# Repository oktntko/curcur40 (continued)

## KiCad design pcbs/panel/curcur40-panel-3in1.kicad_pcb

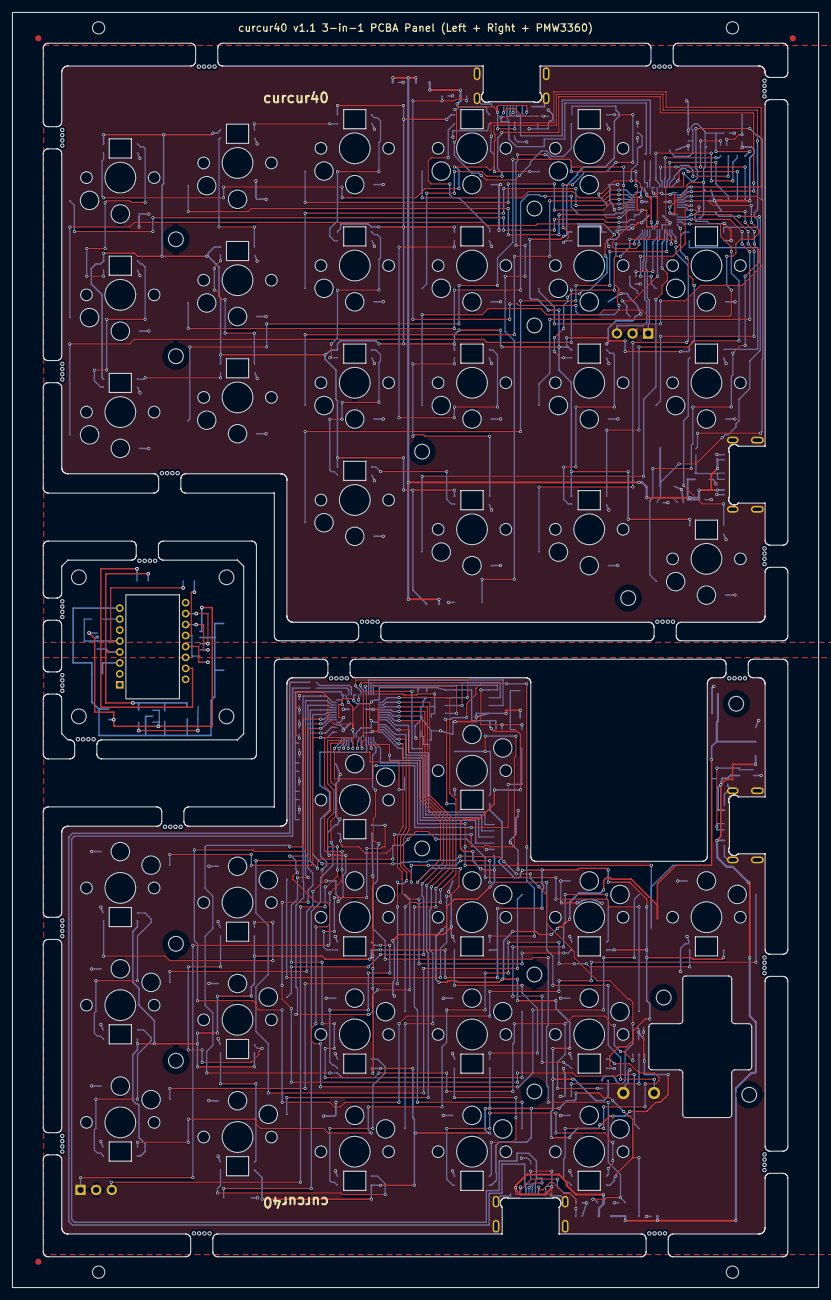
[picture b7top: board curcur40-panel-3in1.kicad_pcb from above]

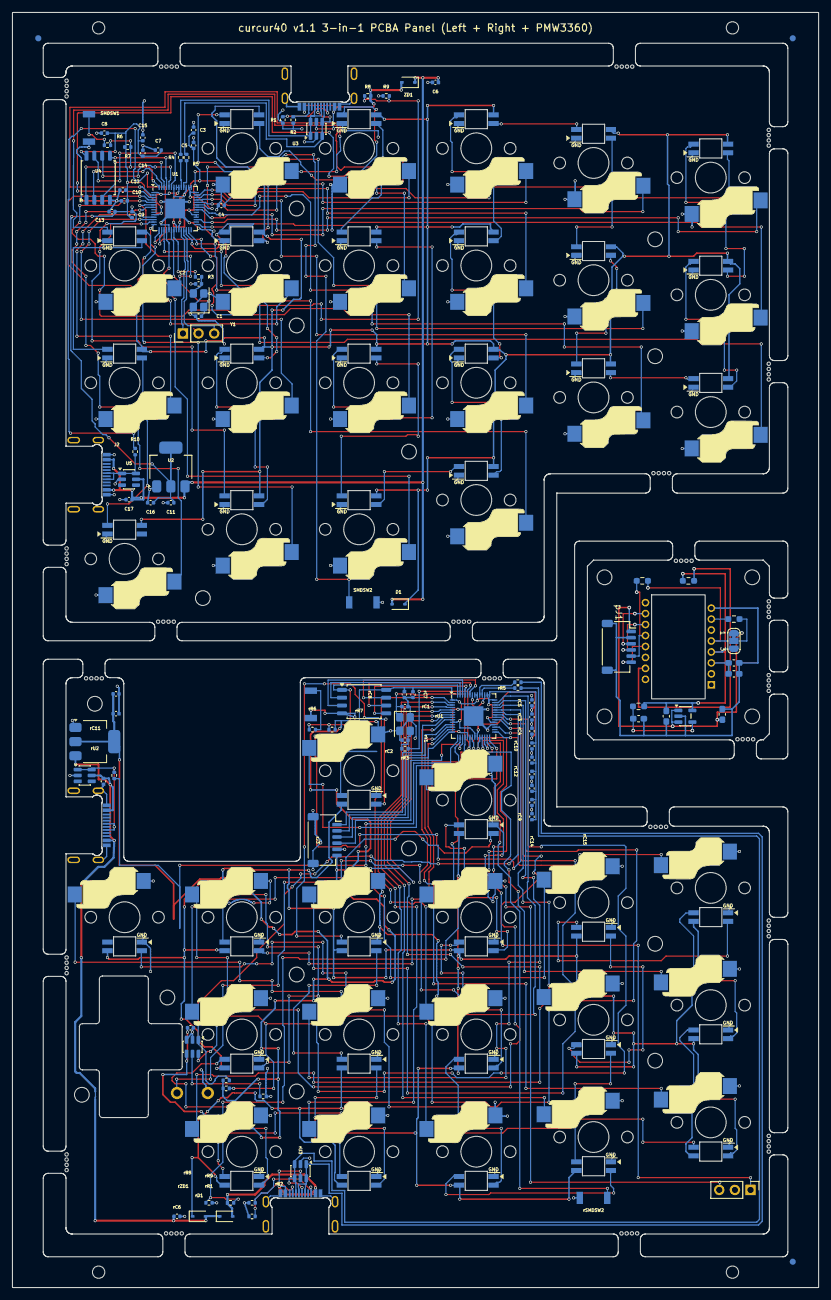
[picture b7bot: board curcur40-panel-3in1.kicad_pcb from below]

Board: 2 copper layers, 131.0 x 207.2 mm, 276 parts (181 on the bottom side), 154 nets.

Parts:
C1, C2: 27p; C_0402_1005Metric
C3, C4, C7, C9, C10, C12, C13, C14, C15: 100n; C_0402_1005Metric
C5, C8, C16, C17: 1u; C_0402_1005Metric
C6, C11: 10u; C_0402_1005Metric
D1: 1N4148WS; D_SOD-323
EXLED1, EXLED2, EXLED3: YS-SK6812MINI-E
EXSW1, EXSW2, EXSW3: SW_Push; keyswitch_choc12_hotswap_1u
FID1_B, FID1_F, FID2_B, FID2_F, FID3_B, FID3_F: Fiducial_1mm_Mask2mm
J1, J2: TYPE-C-31-M-13C; USB_C_Receptacle_TYPE-C-31-M-13C
J4: Conn_01x03; PinHeader_1x03_P2.54mm_Vertical
LED1, LED2, LED3, LED4, LED5, LED6, LED7, LED8, LED9, LED10, LED11, LED12, LED13, LED14, LED15, LED16, LED17, LED18: YS-SK6812MINI-E
MB1, MB2, MB3, MB4, MB5, MB6, MB7, MB8, MB9, MB10, MB11, MB12, MB13, MB14, MB15, MB16, MB17, MB18, MB19, MB20, MB21, MB22, MB23, MB24, MB25, MB26, MB27, MB28, MB29, MB30, MB31, MB32, MB33, MB34, MB35, MB36, MB37, MB38, MB39, MB40, MB41, MB42, MB43, MB44, MB45, MB46, MB47, MB48, MB49, MB50, MB51, MB52, MB53, MB54, MB55, MB56, MB57, MB58, MB59, MB60, MB61, MB62, MB63, MB64, MB65, MB66, MB67, MB68, MB69, MB70, MB71, MB72, MB73, MB74, MB75, MB76, MB77, MB78, MB79, MB80, MB81, MB82, MB83, MB84, MB85, MB86, MB87, MB88: NPTH
R1, R2: 5.1k; R_0402_1005Metric
R3, R6: 1k; R_0402_1005Metric
R4, R5, R10: 27; R_0402_1005Metric
R7: 10k; R_0402_1005Metric
R8: 5.6k; R_0402_1005Metric
R9: 10K; R_0402_1005Metric
SMDSW1, SMDSW2: TS-1088R-02026
SW1, SW2, SW3, SW4, SW5, SW6, SW7, SW8, SW9, SW10, SW11, SW12, SW13, SW14, SW15, SW16, SW17, SW18: SW_Push; keyswitch_choc12_hotswap_1u
TH1, TH2, TH3, TH4: NPTH
U1: RP2040; QFN-56-1EP_7x7mm_P0.4mm_EP3.2x3.2mm
U2: LDL1117S33R; SOT-223-3_TabPin2
U3, U5: USBLC6-2SC6; SOT-23-6
U4: W25Q128JVSIQ; SOIC-8_5.3x5.3mm_P1.27mm
Y1: 12MHz 18pF; Crystal_SMD_3225-4Pin_3.2x2.5mm
ZD1: 1N5819WS; D_SOD-323
pC1: 4.7uF/10V; C_0603_1608Metric_Pad1.08x0.95mm_HandSolder
pC2: 100nF; C_0603_1608Metric_Pad1.08x0.95mm_HandSolder
pC3, pC4: 1uF; C_0603_1608Metric_Pad1.08x0.95mm_HandSolder
pC5: 22nF; C_0603_1608Metric_Pad1.08x0.95mm_HandSolder
pJ1: SM06B-SRSS-TB; JST_SH_SM06B-SRSS-TB_1x06-1MP_P1.00mm_Horizontal
pJP1: SolderJumper_3_Bridged12; SolderJumper-3_P1.3mm_Bridged12_RoundedPad1.0x1.5mm_NumberL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
pR1, pR2: 10k; R_0603_1608Metric_Pad0.98x0.95mm_HandSolder
pR3: 39R; R_0603_1608Metric_Pad0.98x0.95mm_HandSolder
pR4: 28k; R_0603_1608Metric_Pad0.98x0.95mm_HandSolder
pU1: PMW3360DM-T2QU; PMW3360DM-T2QU_16Pin
pU2: TLV74318PDBVR; SOT-23-5
rC1, rC2: 27p; C_0402_1005Metric
rC3, rC4, rC7, rC9, rC10, rC12, rC13, rC14, rC15, rC18: 100n; C_0402_1005Metric
rC5, rC8, rC16, rC17: 1u; C_0402_1005Metric
rC6, rC11: 10u; C_0402_1005Metric
rD1: 1N4148WS; D_SOD-323
rEXLED2: YS-SK6812MINI-E
rEXSW1: Kailh_Square_Silent; Kailh_Square_Silent_6.2x6.2mm
rEXSW2: SW_Push; keyswitch_choc12_hotswap_1u
rJ1, rJ2: TYPE-C-31-M-13C; USB_C_Receptacle_TYPE-C-31-M-13C
rJ3: SM06B-SRSS-TB; JST_SH_SM06B-SRSS-TB_1x06-1MP_P1.00mm_Horizontal
rJ4: Conn_01x03; PinHeader_1x03_P2.54mm_Vertical
rLED2, rLED3, rLED4, rLED5, rLED6, rLED7, rLED8, rLED9, rLED10, rLED11, rLED12, rLED13, rLED14, rLED15, rLED16, rLED17, rLED18: YS-SK6812MINI-E
rR1, rR2: 5.1k; R_0402_1005Metric
rR3, rR6: 1k; R_0402_1005Metric
rR4, rR5, rR10: 27; R_0402_1005Metric
rR7: 10k; R_0402_1005Metric
rR8: 5.6k; R_0402_1005Metric
rR9: 10K; R_0402_1005Metric
rR11, rR12: 4.7k; R_0402_1005Metric
rR13: 0; R_0402_1005Metric
rSMDSW1, rSMDSW2: TS-1088R-02026
rSW2, rSW3, rSW4, rSW5, rSW6, rSW7, rSW8, rSW9, rSW10, rSW11, rSW12, rSW13, rSW14, rSW15, rSW16, rSW17, rSW18: SW_Push; keyswitch_choc12_hotswap_1u
rU1: RP2040; QFN-56-1EP_7x7mm_P0.4mm_EP3.2x3.2mm
rU2: LDL1117S33R; SOT-223-3_TabPin2
rU3, rU5: USBLC6-2SC6; SOT-23-6
rU4: W25Q128JVSIQ; SOIC-8_5.3x5.3mm_P1.27mm
rU6: TMAG5273A1QDBVR; SOT-23-6
rY1: 12MHz 18pF; Crystal_SMD_3225-4Pin_3.2x2.5mm
rZD1: 1N5819WS; D_SOD-323

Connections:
L:+1V1: C3.1, C4.1, C5.1, U1.23, U1.45, U1.50
L:+3V3: C7.1, C8.1, C9.1, C10.1, C11.1, C12.1, C13.1, C14.1, C15.1, C16.1, R7.2, U1.1, U1.10, U1.22, U1.32, U1.33, U1.42, U1.43, U1.44, U1.48, U1.49, U2.2, U4.8
L:+5V: C6.1, C17.1, D1.2, J2.A4 (VBUS), J2.A9 (VBUS), J2.B4 (VBUS), J2.B9 (VBUS), U2.3, U5.5, ZD1.1
L:/D+: J1.A6 (D+), J1.B6 (D+), R4.1, U3.1, U3.6
L:/D-: J1.A7 (D-), J1.B7 (D-), R5.2, U3.3, U3.4
L:/KEY1: SW1.1, U1.14
L:/KEY2: SW2.1, U1.12
L:/KEY3: SW3.1, U1.4
L:/KEY4: SW4.1, U1.2
L:/KEY5: SW5.1, U1.41
L:/KEY6: SW6.1, U1.3
L:/KEY7: SW7.1, U1.5
L:/KEY8: SW8.1, U1.18
L:/KEY9: SW9.1, U1.17
L:/KEY10: SW10.1, U1.40
L:/KEY11: SW11.1, U1.39
L:/KEY12: SW12.1, U1.38
L:/KEY13: SW13.1, U1.35
L:/KEY14: SW14.1, U1.36
L:/KEY15: SW15.1, U1.37
L:/KEY16: SW16.1, U1.27
L:/KEY17: SW17.1, U1.29
L:/KEY18: SW18.1, U1.31
L:/KEYEX1: EXSW1.1, U1.6
L:/KEYEX2: EXSW2.1, U1.11
L:/KEYEX3: EXSW3.1, U1.7
L:/LED: LED1.4, U1.13
L:/QSPI_SCLK: U1.52, U4.6
L:/QSPI_SD0: U1.53, U4.5
L:/QSPI_SD1: U1.55, U4.2
L:/QSPI_SD2: U1.54, U4.3
L:/QSPI_SD3: U1.51, U4.7
L:/QSPI_SS: R6.1, R7.1, U1.56, U4.1
L:/SPLIT_DP: J2.A6 (D+), J2.B6 (D+), R10.1, U5.1, U5.6
L:/SWCLK: J4.1, U1.24
L:/SWD: J4.3, U1.25
L:/TX: R10.2, U1.15
L:/USB_VBUS_PIN: R8.2, R9.1, U1.16
L:GND: C1.2, C2.2, C3.2, C4.2, C5.2, C6.2, C7.2, C8.2, C9.2, C10.2, C11.2, C12.2, C13.2, C14.2, C15.2, C16.2, C17.2, EXLED1.3, EXLED2.3, EXLED3.3, EXSW1.2, EXSW2.2, EXSW3.2, J1.A1 (GND), J1.A12 (GND), J1.B1 (GND), J1.B12 (GND), J1.SH (SHIELD), J2.A1 (GND), J2.A12 (GND), J2.B1 (GND), J2.B12 (GND), J2.SH (SHIELD), J4.2, LED1.3, LED2.3, LED3.3, LED4.3, LED5.3, LED6.3, LED7.3, LED8.3, LED9.3, LED10.3, LED11.3, LED12.3, LED13.3, LED14.3, LED15.3, LED16.3, LED17.3, LED18.3, R1.1, R2.1, R9.2, SMDSW1.1, SMDSW2.1, SW1.2, SW2.2, SW3.2, SW4.2, SW5.2, SW6.2, SW7.2, SW8.2, SW9.2, SW10.2, SW11.2, SW12.2, SW13.2, SW14.2, SW15.2, SW16.2, SW17.2, SW18.2, U1.19, U1.57, U2.1, U3.2, U4.4, U5.2, Y1.2, Y1.4
L:Net-(C2-Pad1): C2.1, R3.1, Y1.3
L:Net-(D1-K): D1.1, EXLED1.1, EXLED2.1, EXLED3.1, LED1.1, LED2.1, LED3.1, LED4.1, LED5.1, LED6.1, LED7.1, LED8.1, LED9.1, LED10.1, LED11.1, LED12.1, LED13.1, LED14.1, LED15.1, LED16.1, LED17.1, LED18.1
L:Net-(EXLED1-DIN): EXLED1.4, LED18.2
L:Net-(EXLED1-DOUT): EXLED1.2, EXLED2.4
L:Net-(EXLED2-DOUT): EXLED2.2, EXLED3.4
L:Net-(J1-CC1): J1.A5 (CC1), R1.2
L:Net-(J1-CC2): J1.B5 (CC2), R2.2
L:Net-(LED1-DOUT): LED1.2, LED2.4
L:Net-(LED2-DOUT): LED2.2, LED3.4
L:Net-(LED3-DOUT): LED3.2, LED4.4
L:Net-(LED4-DOUT): LED4.2, LED5.4
L:Net-(LED5-DOUT): LED5.2, LED6.4
L:Net-(LED6-DOUT): LED6.2, LED7.4
L:Net-(LED7-DOUT): LED7.2, LED8.4
L:Net-(LED8-DOUT): LED8.2, LED9.4
L:Net-(LED10-DIN): LED9.2, LED10.4
L:Net-(LED10-DOUT): LED10.2, LED11.4
L:Net-(LED11-DOUT): LED11.2, LED12.4
L:Net-(LED12-DOUT): LED12.2, LED13.4
L:Net-(LED13-DOUT): LED13.2, LED14.4
L:Net-(LED14-DOUT): LED14.2, LED15.4
L:Net-(LED15-DOUT): LED15.2, LED16.4
L:Net-(LED16-DOUT): LED16.2, LED17.4
L:Net-(LED17-DOUT): LED17.2, LED18.4
L:Net-(R6-Pad2): R6.2, SMDSW1.2
L:Net-(U1-RUN): SMDSW2.2, U1.26
L:Net-(U1-USB_DM): R5.1, U1.46
L:Net-(U1-USB_DP): R4.2, U1.47
L:Net-(U1-XIN): C1.1, U1.20, Y1.1
L:Net-(U1-XOUT): R3.2, U1.21
L:VBUS: J1.A4 (VBUS), J1.A9 (VBUS), J1.B4 (VBUS), J1.B9 (VBUS), R8.1, U3.5, ZD1.2
P:+3V3R: pC3.1, pJ1.1, pJP1.1, pU2.1, pU2.3
P:/+1V8_PMW: pC4.1, pJP1.3, pR3.1, pR4.1, pU1.4 (VDD), pU2.5
P:/MISO: pJ1.5, pR2.2, pU1.12 (MISO)
P:/MOSI: pJ1.4, pU1.11 (MOSI)
P:/NCS: pJ1.6, pU1.13 (~CS)
P:/RESET: pR1.2, pU1.7 (~RESET)
P:/SCLK: pJ1.3, pU1.10 (SCLK)
P:/V_{IO}: pJP1.2, pR1.1, pR2.1, pU1.5 (VDDIO)
P:GNDR: pC1.2, pC2.2, pC3.2, pC4.2, pC5.2, pJ1.2, pJ1.MP, pU1.8 (GND), pU2.2
P:Net-(U1-LED_P): pR3.2, pU1.15 (LED_P)
P:Net-(U1-VDDPIX): pC1.1, pC2.1, pU1.3 (VDDPIX)
P:Net-(U2-NC): pC5.1, pR4.2, pU2.4
R:+1V1R: rC3.1, rC4.1, rC5.1, rU1.23, rU1.45, rU1.50
R:+3V3R: rC7.1, rC8.1, rC9.1, rC10.1, rC11.1, rC12.1, rC13.1, rC14.1, rC15.1, rC16.1, rC18.1, rJ3.6, rR7.2, rR11.1, rR12.1, rU1.1, rU1.10, rU1.22, rU1.33, rU1.42, rU1.43, rU1.44, rU1.48, rU1.49, rU2.2, rU4.8, rU6.4
R:+5VR: rC6.1, rC17.1, rD1.2, rJ2.A4 (VBUS), rJ2.A9 (VBUS), rJ2.B4 (VBUS), rJ2.B9 (VBUS), rU2.3, rU5.5, rZD1.1
R:/D+: rJ1.A6 (D+), rJ1.B6 (D+), rR4.1, rU3.1, rU3.6
R:/D-: rJ1.A7 (D-), rJ1.B7 (D-), rR5.2, rU3.3, rU3.4
R:/KEY2: rSW2.1, rU1.34
R:/KEY3: rSW3.1, rU1.38
R:/KEY4: rSW4.1, rU1.39
R:/KEY5: rSW5.1, rU1.3
R:/KEY6: rSW6.1, rU1.40
R:/KEY7: rSW7.1, rU1.31
R:/KEY8: rSW8.1, rU1.28
R:/KEY9: rSW9.1, rU1.27
R:/KEY10: rSW10.1, rU1.41
R:/KEY11: rSW11.1, rU1.2
R:/KEY12: rSW12.1, rU1.4
R:/KEY13: rSW13.1, rU1.5
R:/KEY14: rSW14.1, rU1.6
R:/KEY15: rSW15.1, rU1.7
R:/KEY16: rSW16.1, rU1.29
R:/KEY17: rSW17.1, rU1.18
R:/KEY18: rSW18.1, rU1.12
R:/KEYEX1: rEXSW1.1, rU1.9
R:/KEYEX2: rEXSW2.1, rU1.35
R:/LED: rLED2.4, rU1.13
R:/MISO: rJ3.2, rU1.11
R:/MOSI: rJ3.3, rU1.14
R:/NCS: rJ3.1, rU1.8
R:/QSPI_SCLK: rU1.52, rU4.6
R:/QSPI_SD0: rU1.53, rU4.5
R:/QSPI_SD1: rU1.55, rU4.2
R:/QSPI_SD2: rU1.54, rU4.3
R:/QSPI_SD3: rU1.51, rU4.7
R:/QSPI_SS: rR6.1, rR7.1, rU1.56, rU4.1
R:/SCLK: rJ3.4, rU1.17
R:/SPLIT_DP: rJ2.A6 (D+), rJ2.B6 (D+), rR10.1, rU5.1, rU5.6
R:/SWCLK: rJ4.1, rU1.24
R:/SWD: rJ4.3, rU1.25
R:/TX: rR10.2, rU1.15
R:/USB_VBUS_PIN: rR8.2, rR9.1, rU1.16
R:/WHEEL_SCL: rR12.2, rU1.37, rU6.1
R:/WHEEL_SDA: rR11.2, rU1.36, rU6.6
R:GNDR: rC1.2, rC2.2, rC3.2, rC4.2, rC5.2, rC6.2, rC7.2, rC8.2, rC9.2, rC10.2, rC11.2, rC12.2, rC13.2, rC14.2, rC15.2, rC16.2, rC17.2, rC18.2, rEXLED2.3, rEXSW1.2, rEXSW2.2, rJ1.A1 (GND), rJ1.A12 (GND), rJ1.B1 (GND), rJ1.B12 (GND), rJ1.SH (SHIELD), rJ2.A1 (GND), rJ2.A12 (GND), rJ2.B1 (GND), rJ2.B12 (GND), rJ2.SH (SHIELD), rJ3.5, rJ3.MP, rJ4.2, rLED2.3, rLED3.3, rLED4.3, rLED5.3, rLED6.3, rLED7.3, rLED8.3, rLED9.3, rLED10.3, rLED11.3, rLED12.3, rLED13.3, rLED14.3, rLED15.3, rLED16.3, rLED17.3, rLED18.3, rR1.1, rR2.1, rR9.2, rR13.2, rSMDSW1.1, rSMDSW2.1, rSW2.2, rSW3.2, rSW4.2, rSW5.2, rSW6.2, rSW7.2, rSW8.2, rSW9.2, rSW10.2, rSW11.2, rSW12.2, rSW13.2, rSW14.2, rSW15.2, rSW16.2, rSW17.2, rSW18.2, rU1.19, rU1.32, rU1.57, rU2.1, rU3.2, rU4.4, rU5.2, rU6.2, rU6.3, rY1.2, rY1.4
R:Net-(rC2-Pad1): rC2.1, rR3.1, rY1.3
R:Net-(rD1-K): rD1.1, rEXLED2.1, rLED2.1, rLED3.1, rLED4.1, rLED5.1, rLED6.1, rLED7.1, rLED8.1, rLED9.1, rLED10.1, rLED11.1, rLED12.1, rLED13.1, rLED14.1, rLED15.1, rLED16.1, rLED17.1, rLED18.1
R:Net-(rEXLED2-DIN): rEXLED2.4, rLED18.2
R:Net-(rJ1-CC1): rJ1.A5 (CC1), rR1.2
R:Net-(rJ1-CC2): rJ1.B5 (CC2), rR2.2
R:Net-(rLED2-DOUT): rLED2.2, rLED3.4
R:Net-(rLED3-DOUT): rLED3.2, rLED4.4
R:Net-(rLED4-DOUT): rLED4.2, rLED5.4
R:Net-(rLED5-DOUT): rLED5.2, rLED6.4
R:Net-(rLED6-DOUT): rLED6.2, rLED7.4
R:Net-(rLED7-DOUT): rLED7.2, rLED8.4
R:Net-(rLED8-DOUT): rLED8.2, rLED9.4
R:Net-(rLED10-DIN): rLED9.2, rLED10.4
R:Net-(rLED10-DOUT): rLED10.2, rLED11.4
R:Net-(rLED11-DOUT): rLED11.2, rLED12.4
R:Net-(rLED12-DOUT): rLED12.2, rLED13.4
R:Net-(rLED13-DOUT): rLED13.2, rLED14.4
R:Net-(rLED14-DOUT): rLED14.2, rLED15.4
R:Net-(rLED15-DOUT): rLED15.2, rLED16.4
R:Net-(rLED16-DOUT): rLED16.2, rLED17.4
R:Net-(rLED17-DOUT): rLED17.2, rLED18.4
R:Net-(rR6-Pad2): rR6.2, rSMDSW1.2
R:Net-(rU1-RUN): rSMDSW2.2, rU1.26
R:Net-(rU1-USB_DM): rR5.1, rU1.46
R:Net-(rU1-USB_DP): rR4.2, rU1.47
R:Net-(rU1-XIN): rC1.1, rU1.20, rY1.1
R:Net-(rU1-XOUT): rR3.2, rU1.21
R:Net-(rU6-~INT): rR13.1, rU6.5
R:VBUSR: rJ1.A4 (VBUS), rJ1.A9 (VBUS), rJ1.B4 (VBUS), rJ1.B9 (VBUS), rR8.1, rU3.5, rZD1.2

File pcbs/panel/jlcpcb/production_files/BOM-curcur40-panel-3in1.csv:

Comment,Designator,Footprint,LCSC
W25Q128JVSIQ,"U4,rU4",SOIC-8_5.3x5.3mm_P1.27mm,C113767
1k,"R3,R6,rR3,rR6",R_0402_1005Metric,C11702
100nF,pC2,C_0603_1608Metric,C14663
100n,"C10,C12,C13,C14,C15,C17,C3,C4,C7,C9,rC10,rC12,rC13,rC14,rC15,rC17,rC18,rC3,rC4,rC7,rC9",C_0402_1005Metric,C1525
10u,"C11,C6,rC11,rC6",C_0402_1005Metric,C15525
27p,"C1,C2,rC1,rC2",C_0402_1005Metric,C1557
1uF,"pC3,pC4",C_0603_1608Metric,C15849
SM06B-SRSS-TB(LF)(SN),"pJ1,rJ3",JST_SH_SM06B-SRSS-TB_1x06-1MP_P1.00mm_Horizontal,C160405
0,rR13,R_0402_1005Metric,C17168
1N5819WS,"ZD1,rZD1",D_SOD-323,C191023
4.7uF/10V,pC1,C_0603_1608Metric,C19666
RP2040,"U1,rU1",QFN-56-1EP_7x7mm_P0.4mm_EP3.2x3.2mm,C2040
1N4148WS,"D1,rD1",D_SOD-323,C2128
39R,pR3,R_0603_1608Metric,C23154
10k,"R7,R9,rR7,rR9",R_0402_1005Metric,C25744
10k,"pR1,pR2",R_0603_1608Metric,C25804
4.7k,"rR11,rR12",R_0402_1005Metric,C25900
5.1k,"R1,R2,rR1,rR2",R_0402_1005Metric,C25905
5.6k,"R8,rR8",R_0402_1005Metric,C25908
TYPE-C-31-M-13C,"J1,J2,rJ1,rJ2",TYPE-C-31-M-13C,C2848620
27,"R10,R4,R5,rR10,rR4,rR5",R_0402_1005Metric,C2909343
TMAG5273A1QDBVR,rU6,SOT-23-6,C3716049
LDL1117S33R,"U2,rU2",SOT-223-3_TabPin2,C435835
TS-1088R-02026,"SMDSW1,SMDSW2,rSMDSW1,rSMDSW2",TS-1088R-02026,C455280
TLV74318PDBVR,pU2,SOT-23-5,C485152
YS-SK6812MINI-E,"EXLED1,EXLED2,EXLED3,LED1,LED10,LED11,LED12,LED13,LED14,LED15,LED16,LED17,LED18,LED2,LED3,LED4,LED5,LED6,LED7,LED8,LED9,rEXLED2,rLED10,rLED11,rLED12,rLED13,rLED14,rLED15,rLED16,rLED17,rLED18,rLED2,rLED3,rLED4,rLED5,rLED6,rLED7,rLED8,rLED9",YS-SK6812MINI-E,C5149201
1u,"C16,C5,C8,rC16,rC5,rC8",C_0402_1005Metric,C52923
SW_Push,"EXSW1,EXSW2,EXSW3,SW1,SW10,SW11,SW12,SW13,SW14,SW15,SW16,SW17,SW18,SW2,SW3,SW4,SW5,SW6,SW7,SW8,SW9,rEXSW2,rSW10,rSW11,rSW12,rSW13,rSW14,rSW15,rSW16,rSW17,rSW18,rSW2,rSW3,rSW4,rSW5,rSW6,rSW7,rSW8,rSW9",keyswitch_choc12_hotswap_1u,C5333465
USBLC6-2SC6,"U3,U5,rU3,rU5",SOT-23-6,C7519
12MHz 18pF,"Y1,rY1",Crystal_SMD_3225-4Pin_3.2x2.5mm,C91749

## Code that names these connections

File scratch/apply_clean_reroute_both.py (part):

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        if net == "GNDR" and abs(sx - 111.5625) < 0.2 and abs(sy - 36.82625) < 0.2:
            to_delete.append(t)

        # Remove /KEY16 and /KEY17 tracks near pinky hole (98.0, 38.0)
        if net in ["/KEY16", "/KEY17"] and min(sx, ex) > 89.0 and max(sx, ex) < 102.0 and min(sy, ey) > 34.0 and max(sy, ey) < 41.0:
            to_delete.append(t)

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        if net == "+5V" and abs(sx - (-6.5425)) < 0.1 and abs(ex - (-6.5425)) < 0.1 and min(sy, ey) < 38.6 and max(sy, ey) > 30.7:
            to_delete.append(t)

        # Remove /KEY16, /KEY17, /KEY18 tracks near pinky hole (-98.0, 38.0)
        if net in ["/KEY16", "/KEY17", "/KEY18"] and min(sx, ex) > -103.0 and max(sx, ex) < -89.0 and min(sy, ey) > 34.0 and max(sy, ey) < 41.0:
            to_delete.append(t)

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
